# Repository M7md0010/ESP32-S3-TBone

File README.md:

<h1 align="center">ESP32-S3-TBone</h1>

<p align="center">
  <em>Custom T-bone form-factor ESP32-S3 development board engineered to resolve solderless breadboard real estate constraints by exposing dual-sided tie points.</em>
</p>

---

## 📋 Project Overview

The **ESP32-S3-TBone** is a purpose-engineered development board built around the **ESP32-S3-WROOM-1** module. Unlike standard rectangular devkits that monopolize the entire breadboard, the T-bone form factor features a narrowed neck section that straddles the center channel while the head section extends beyond the breadboard edge — freeing up **both sides** of the breadboard for prototyping access to all GPIO tie points.

### Key Design Goals

- **Maximize breadboard usable area** — dual-sided tie point access for all broken-out GPIOs.
- **Signal integrity first** — 4-layer controlled-impedance stackup with dedicated ground and power reference planes.
- **Manufacturing ready** — Gerber-optimized output with DFM rule compliance for standard PCB fabs (JLCPCB, PCBWay, Norisolutions).
- **Mechanical validation** — 3D collision-checked against standard 830-point breadboard models in Fusion 360.

---

## 🏗️ Hardware Architecture & Stackup

### MCU: ESP32-S3-WROOM-1

| Parameter        | Specification                           |
| ---------------- | --------------------------------------- |
| Core             | Xtensa® dual-core 32-bit LX7           |
| Clock            | Up to 240 MHz                           |
| Flash            | 16 MB (Quad SPI)                        |
| SRAM             | 512 KB                                  |
| Connectivity     | Wi-Fi 802.11 b/g/n + Bluetooth 5 (LE)  |
| USB              | Native USB 2.0 OTG + UART via CH343P   |
| GPIO             | Fully broken-out via dual header rows   |

### Onboard Hardware Features & Peripherals

- **I2C Interface:** Dedicated extracted socket/pins for fast and reliable I2C peripheral expansion.
- **Servo Motor Headers:** Onboard header pins specifically broken out for direct servo motor control.
- **Addressable RGB LEDs:** 2× onboard WS2812B RGB LEDs for customizable status indication and visual feedback.
- **Flexible Power Inputs:** Power the board via either of the USB Type-C ports or directly through the header pins.
- **Switchable Breadboard Power Rails:** Two mechanically fit pins designed to drop directly into the breadboard's power rails. Features a dedicated toggle switch to select between **3.3V** and **5V** logic levels for the breadboard.
- **Main Power Switch:** Dedicated ON/OFF toggle switch for main board power.
- **Programmable User Button:** A custom tactile push button hooked up with a pull resistor, ready to be programmed for user input.
- **PTC Thermistors:** Onboard resettable fuses for robust overcurrent protection.

### 4-Layer PCB Stackup

```
┌─────────────────────────────────────────────────────────┐
│  Layer 1 — F.Cu (Top)                                   │
│  → High-density signal routing, component pads,         │
│    USB differential pairs, crystal oscillator traces     │
├─────────────────────────────────────────────────────────┤
│  Layer 2 — In1.Cu (Inner 1)                             │
│  → Solid continuous ground (GND) reference plane        │
│    Provides low-impedance return path for all signals   │
├─────────────────────────────────────────────────────────┤
│  Layer 3 — In2.Cu (Inner 2)                             │
│  → Partitioned low-impedance power planes               │
│    • 3V3 polygon pour — main logic supply               │
│    • 5V rail — USB VBUS passthrough                     │
│    • VBUS — upstream USB input power                    │
├─────────────────────────────────────────────────────────┤
│  Layer 4 — B.Cu (Bottom)                                │
│  → Bottom interconnects, ground return stitching,       │
│    thermal relief pads, and auxiliary signal routing     │
└─────────────────────────────────────────────────────────┘
```

---

## 🔧 Design For Manufacturability (DFM) & Layout

### EMI Shielding — Perimeter Via Stitching
A continuous array of stitching vias along the board perimeter connects the top and bottom ground pours, forming a **Faraday cage** effect. This:
- Contains return currents within the board stackup
- Reduces edge-radiated EMI emissions
- Improves ground plane continuity at board boundaries

### Neck Corner Geometry — CNC Routing Clearance
The interior corners at the T-bone neck-to-head transition use **chamfered/radiused fillets** to accommodate standard CNC routing bit diameters (≥ 0.8 mm). Sharp 90° interior corners are physically impossible to mill and would cause fabrication rejects.

### Soldermask-Clipped Silkscreen
The `--subtract-soldermask` flag was used during Gerber generation to automatically **clip silkscreen artwork** wherever it overlaps exposed copper pads. This prevents:
- Ink-on-pad contamination during soldering
- Poor solder wetting on component pads
- IPC-A-610 Class 2/3 violations

### USB Type-C CC Pull-Down Logic
Both USB-C ports implement the correct **CC1/CC2 pull-down resistor** network (5.1 kΩ to GND) on each Configuration Channel pin, advertising the device as a **UFP (Upstream Facing Port)** sink per USB Type-C spec Rev 2.0. This ensures reliable cable detection and power negotiation with all USB-C hosts and chargers.

---

## 🧊 Mechanical Validation

The board outline (exported as `.step` from KiCad) was imported into **Autodesk Fusion 360** alongside a reference breadboard CAD model to perform:

1. **Collision detection** — verify zero interference between the PCB body and breadboard clips/housing.
2. **Tie-point clearance** — confirm all header pins align with breadboard hole pitch (2.54 mm / 0.1").
3. **Overhang validation** — ensure the head section clears the breadboard edge without cantilever instability.

---

## 📸 Gallery

| Front (3D Render) | Back (3D Render) |
|---|---|
|  |  |

| Front (No Components) | Back (No Components) |
|---|---|
|  |  |

---

## 📁 Directory Structure

```
ESP32-S3-TBone/
├── hardware/
│   ├── schematics/
│   │   ├── schematic.pdf            # Exported schematic drawing (PDF)
│   │   └── v1.0.kicad_sch           # KiCad schematic source
│   ├── pcb/
│   │   ├── v1.0.kicad_pcb           # KiCad PCB layout source
│   │   ├── v1.0.kicad_pro           # KiCad project file
│   │   └── v1.0.kicad_dru           # KiCad design rules
│   ├── gerbers/
│   │   ├── gerbers.zip              # Production-ready Gerber + Drill archive
│   │   ├── v1.0-F_Cu.gtl            # Front copper
│   │   ├── v1.0-In1_Cu.g1           # Inner layer 1 (GND plane)
│   │   ├── v1.0-In2_Cu.g2           # Inner layer 2 (Power planes)
│   │   ├── v1.0-B_Cu.gbl            # Back copper
│   │   ├── v1.0-F_Mask.gts          # Front solder mask
│   │   ├── v1.0-B_Mask.gbs          # Back solder mask
│   │   ├── v1.0-F_Silkscreen.gto    # Front silkscreen
│   │   ├── v1.0-B_Silkscreen.gbo    # Back silkscreen
│   │   ├── v1.0-Edge_Cuts.gm1       # Board outline
│   │   ├── v1.0.drl                 # Excellon drill file
│   │   ├── v1.0-drl_map.gbr         # Drill map (Gerber X2)
│   │   └── ...                      # Additional fabrication layers
│   └── mechanical/
│       ├── ESP32-S3-TBone.step       # 3D STEP assembly export
│       ├── Breadboard.fbx            # Breadboard reference model
│       └── breadboard-reference.glb  # Breadboard GLB model
├── docs/
│   └── images/
│       ├── 3d-front.png              # Front 3D render
│       ├── 3d-back.png               # Back 3D render
│       ├── 3d-front-no-components.png
│       ├── 3d-back-no-components.png
│       ├── breadboard-fit.png        # Breadboard fit verification
│       └── comparison.png            # Size comparison
├── .gitignore
├── LICENSE                            # MIT License
└── README.md                          # This file
```

---

## 🛠️ Regenerating Manufacturing Files

If you modify the KiCad source files, regenerate all outputs using `kicad-cli`:

```bash
# Gerber layers (with soldermask-clipped silkscreen)
kicad-cli pcb export gerbers --subtract-soldermask \
  -o hardware/gerbers/ hardware/pcb/v1.0.kicad_pcb

# Excellon drill files + Gerber X2 drill map
kicad-cli pcb export drill --generate-map --map-format gerberx2 \
  -o hardware/gerbers/ hardware/pcb/v1.0.kicad_pcb

# Schematic PDF
kicad-cli sch export pdf \
  -o hardware/schematics/schematic.pdf hardware/schematics/v1.0.kicad_sch

# STEP 3D assembly (skip DNP, substitute models)
kicad-cli pcb export step --no-dnp --subst-models \
  -o hardware/mechanical/ESP32-S3-TBone.step hardware/pcb/v1.0.kicad_pcb
```

---

## 📜 License

This project is licensed under the **MIT License** — see the [LICENSE](./LICENSE) file for details.

---

<p align="center">
  <sub>Designed & engineered by <a href="https://github.com/M7md0010">@M7md0010</a></sub>
</p>

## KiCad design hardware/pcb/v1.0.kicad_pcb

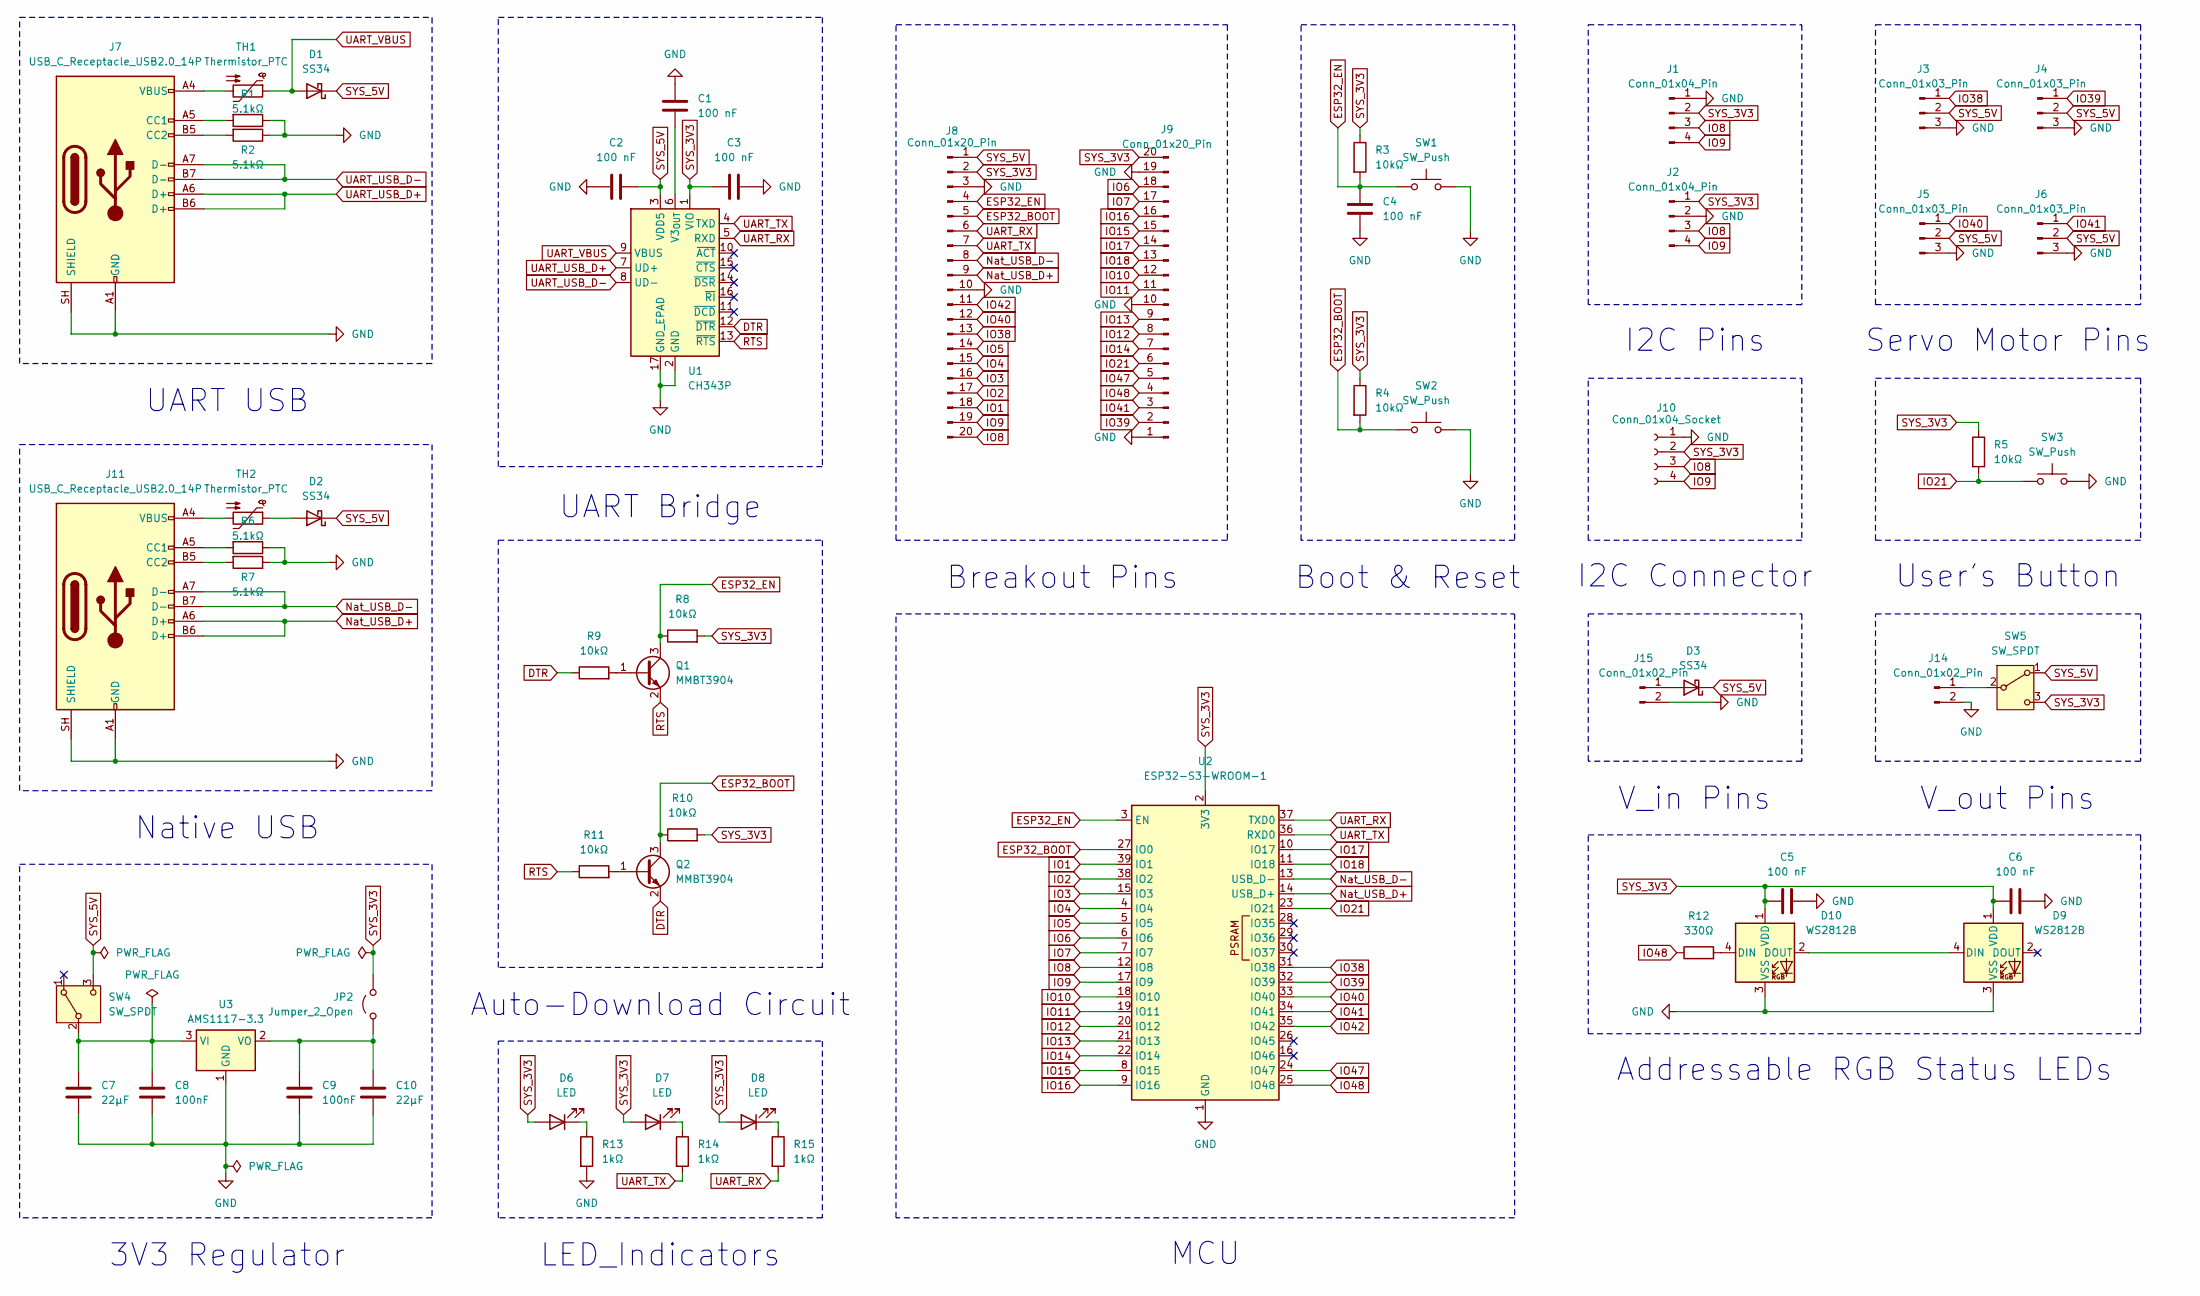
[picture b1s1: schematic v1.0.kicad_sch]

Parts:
C1, C2, C3, C4, C5, C6: 100 nF; C_0201_0603Metric
C7, C10: 22μF; C_1206_3216Metric
C8, C9: 100nF; C_0201_0603Metric
D1, D2, D3: SS34; D_SMA
D6, D7, D8: LED; LED_0805_2012Metric
D9, D10: WS2812B; LED_WS2812B_PLCC4_5.0x5.0mm_P3.2mm
J1, J2: Conn_01x04_Pin; PinSocket_1x04_P2.54mm_Vertical
J3, J4, J5, J6: Conn_01x03_Pin; PinHeader_1x03_P2.54mm_Vertical
J7, J11: USB_C_Receptacle_USB2.0_14P; USB_C_Receptacle_HRO_TYPE-C-31-M-12
J8, J9: Conn_01x20_Pin; PinHeader_1x20_P2.54mm_Vertical
J10: Conn_01x04_Socket; JST_EH_S4B-EH_1x04_P2.50mm_Horizontal
J14, J15: Conn_01x02_Pin; PinHeader_1x02_P2.54mm_Vertical
JP2: Jumper_2_Open; SolderJumper-2_P1.3mm_Open_RoundedPad1.0x1.5mm
Q1, Q2: MMBT3904; SOT-23
R1, R2, R6, R7: 5.1kΩ; R_0603_1608Metric
R3, R4, R5, R8, R9, R10, R11: 10kΩ; R_0603_1608Metric
R12: 330Ω; R_0603_1608Metric
R13, R14, R15: 1kΩ; R_0603_1608Metric
SW1, SW2, SW3: SW_Push; SW_SPST_PTS645Sx43SMTR92
SW4: SW_SPDT; SW_SPDT_PCM12
SW5: SW_SPDT; SW_Slide_SPDT_Straight_CK_OS102011MS2Q
TH1, TH2: Thermistor_PTC; Fuse_1206_3216Metric
U1: CH343P; WCH_QFN-16-1EP_3x3mm_P0.5mm_EP1.8x1.8mm
U2: ESP32-S3-WROOM-1
U3: AMS1117-3.3; SOT-223-3_TabPin2

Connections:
DTR: Q2.2 (E), R9.1, U1.12 (~DTR)
ESP32_BOOT: J8.5, Q2.3 (C), R4.2, R10.1, SW2.1, U2.27 (IO0)
ESP32_EN: C4.1, J8.4, Q1.3 (C), R3.2, R8.1, SW1.1, U2.3 (EN)
GND: C1.1, C2.2, C3.1, C4.2, C5.1, C6.1, C7.2, C8.2, C9.2, C10.2, D9.3 (VSS), D10.3 (VSS), J1.1, J2.2, J3.3, J4.3, J5.3, J6.3, J7.A1 (GND), J7.A12 (GND), J7.B1 (GND), J7.B12 (GND), J7.SH (SHIELD), J8.3, J8.10, J9.1, J9.10, J9.19, J10.1, J11.A1 (GND), J11.A12 (GND), J11.B1 (GND), J11.B12 (GND), J11.SH (SHIELD), J14.2, J15.2, R1.1, R2.1, R6.1, R7.1, R13.2, SW1.2, SW2.2, SW3.2, U1.2 (GND), U1.17 (GND_EPAD), U2.1 (GND), U2.40 (GND), U2.41 (GND), U3.1 (GND)
IO1: J8.18, U2.39 (IO1)
IO2: J8.17, U2.38 (IO2)
IO3: J8.16, U2.15 (IO3)
IO4: J8.15, U2.4 (IO4)
IO5: J8.14, U2.5 (IO5)
IO6: J9.18, U2.6 (IO6)
IO7: J9.17, U2.7 (IO7)
IO8: J1.3, J2.3, J8.20, J10.3, U2.12 (IO8)
IO9: J1.4, J2.4, J8.19, J10.4, U2.17 (IO9)
IO10: J9.12, U2.18 (IO10)
IO11: J9.11, U2.19 (IO11)
IO12: J9.8, U2.20 (IO12)
IO13: J9.9, U2.21 (IO13)
IO14: J9.7, U2.22 (IO14)
IO15: J9.15, U2.8 (IO15)
IO16: J9.16, U2.9 (IO16)
IO17: J9.14, U2.10 (IO17)
IO18: J9.13, U2.11 (IO18)
IO21: J9.6, R5.2, SW3.1, U2.23 (IO21)
IO38: J3.1, J8.13, U2.31 (IO38)
IO39: J4.1, J9.2, U2.32 (IO39)
IO40: J5.1, J8.12, U2.33 (IO40)
IO41: J6.1, J9.3, U2.34 (IO41)
IO42: J8.11, U2.35 (IO42)
IO47: J9.5, U2.24 (IO47)
IO48: J9.4, R12.1, U2.25 (IO48)
Nat_USB_D+: J8.9, J11.A6 (D+), J11.B6 (D+), U2.14 (USB_D+)
Nat_USB_D-: J8.8, J11.A7 (D-), J11.B7 (D-), U2.13 (USB_D-)
unnamed: D2.2 (A), TH2.1
unnamed: D3.2 (A), J15.1
unnamed: D6.1 (K), R13.1
unnamed: D7.1 (K), R14.1
unnamed: D8.1 (K), R15.1
unnamed: D10.4 (DIN), R12.2
unnamed: D9.4 (DIN), D10.2 (DOUT)
unnamed: J7.A5 (CC1), R1.2
unnamed: J7.B5 (CC2), R2.2
unnamed: J7.A4 (VBUS), J7.A9 (VBUS), J7.B4 (VBUS), J7.B9 (VBUS), TH1.2
unnamed: J11.A5 (CC1), R6.2
unnamed: J11.B5 (CC2), R7.2
unnamed: J11.A4 (VBUS), J11.A9 (VBUS), J11.B4 (VBUS), J11.B9 (VBUS), TH2.2
unnamed: J14.1, SW5.2 (B)
unnamed: C9.1, C10.1, JP2.1 (A), U3.2 (VO)
unnamed: Q1.1 (B), R9.2
unnamed: Q2.1 (B), R11.2
unnamed: C7.1, C8.1, SW4.2 (B), U3.3 (VI)
unnamed: C1.2, U1.6 (V3_{OUT})
RTS: Q1.2 (E), R11.1, U1.13 (~RTS)
SYS_3V3: C3.2, C5.2, C6.2, D6.2 (A), D7.2 (A), D8.2 (A), D9.1 (VDD), D10.1 (VDD), J1.2, J2.1, J8.2, J9.20, J10.2, JP2.2 (B), R3.1, R4.1, R5.1, R8.2, R10.2, SW5.3 (C), U1.1 (VIO), U2.2 (3V3)
SYS_5V: C2.1, D1.1 (K), D2.1 (K), D3.1 (K), J3.2, J4.2, J5.2, J6.2, J8.1, SW4.3 (C), SW5.1 (A), U1.3 (VDD5)
UART_RX: J8.6, R15.2, U1.5 (RXD), U2.37 (TXD0)
UART_TX: J8.7, R14.2, U1.4 (TXD), U2.36 (RXD0)
UART_USB_D+: J7.A6 (D+), J7.B6 (D+), U1.7 (UD+)
UART_USB_D-: J7.A7 (D-), J7.B7 (D-), U1.8 (UD-)
UART_VBUS: D1.2 (A), TH1.1, U1.9 (VBUS)

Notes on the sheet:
Servo Motor Pins
Auto-Download Circuit
UART USB
MCU
LED_Indicators
3V3 Regulator
Boot & Reset
Breakout Pins
UART Bridge
Native USB
User's Button
I2C Connector
V_in Pins
I2C Pins
Addressable RGB Status LEDs
V_out Pins

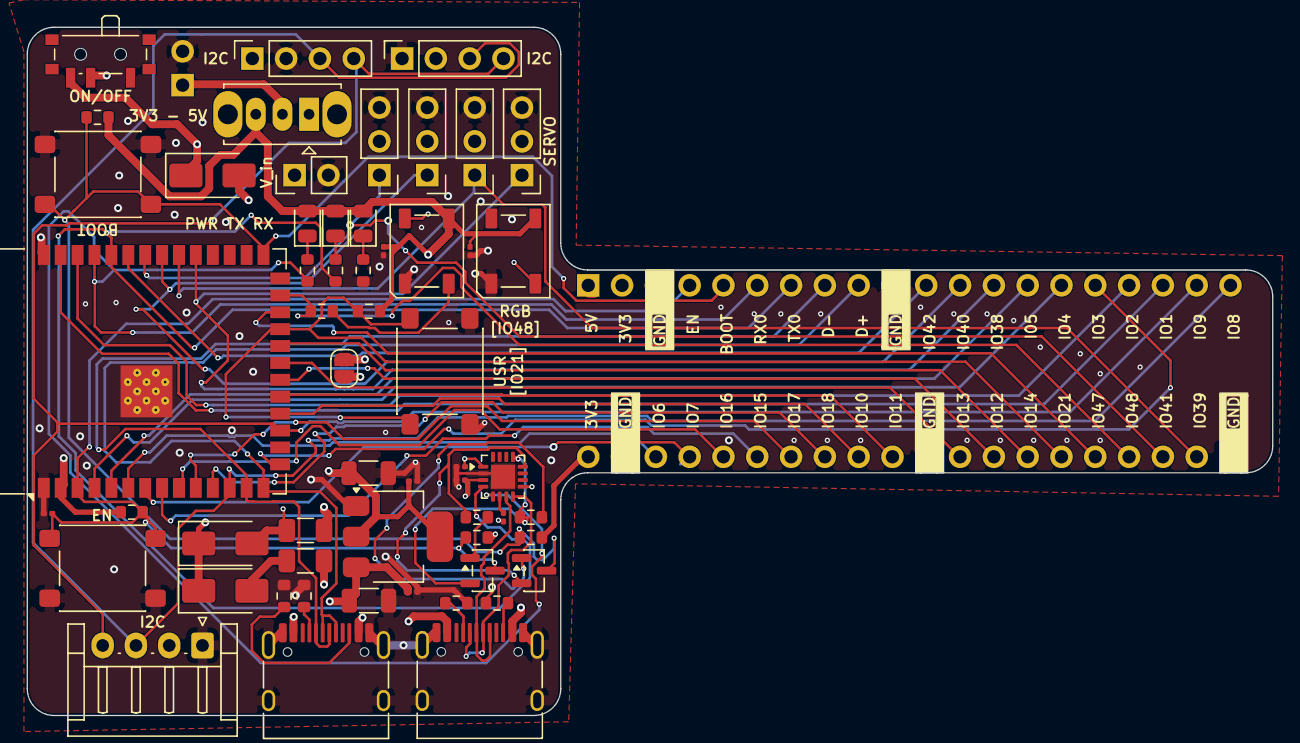
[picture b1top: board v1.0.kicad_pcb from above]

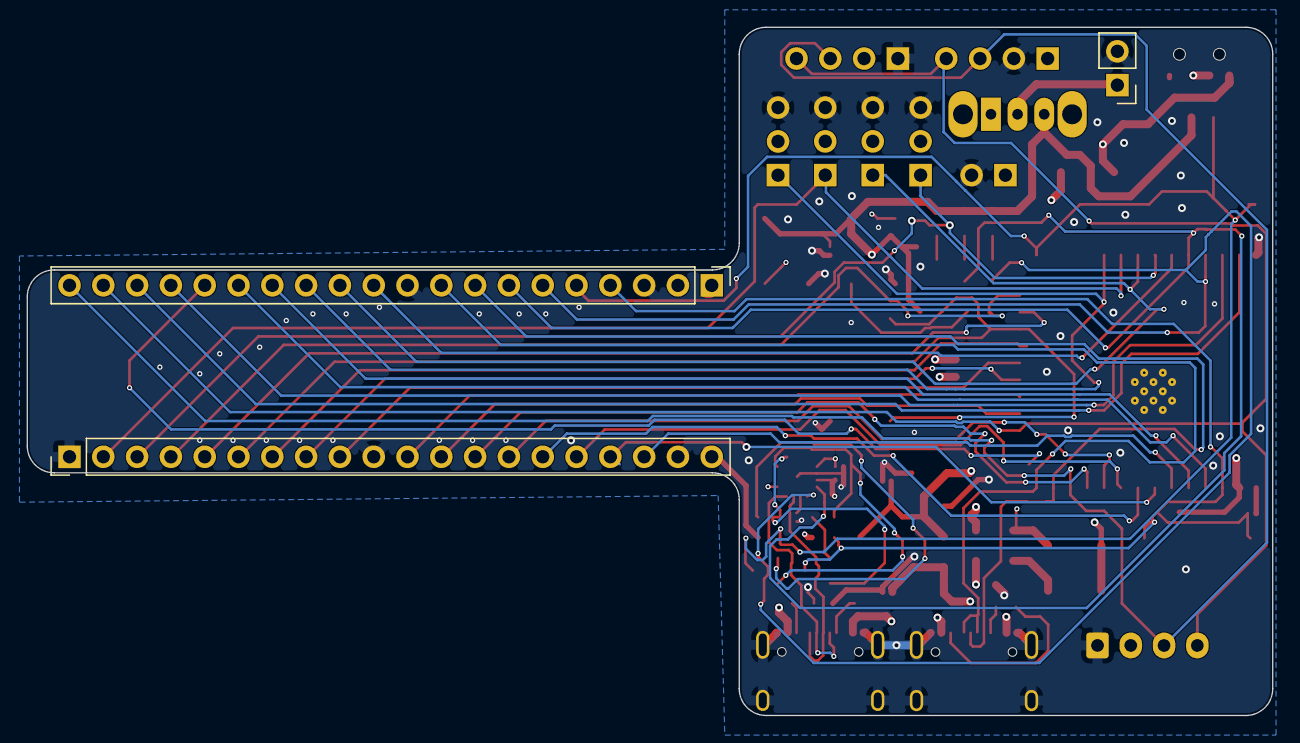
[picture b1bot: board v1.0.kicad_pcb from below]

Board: 4 copper layers, 93.6 x 51.7 mm, 59 parts (3 on the bottom side), 59 nets.

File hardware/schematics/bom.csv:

"Refs","Value","Footprint","Qty","DNP"
"C1","100 nF","Capacitor_SMD:C_0201_0603Metric","1",""
"C2","100 nF","Capacitor_SMD:C_0201_0603Metric","1",""
"C3","100 nF","Capacitor_SMD:C_0201_0603Metric","1",""
"C4","100 nF","Capacitor_SMD:C_0201_0603Metric","1",""
"C5","100 nF","Capacitor_SMD:C_0201_0603Metric","1",""
"C6","100 nF","Capacitor_SMD:C_0201_0603Metric","1",""
"C7","22μF","Capacitor_SMD:C_1206_3216Metric","1",""
"C8","100nF","Capacitor_SMD:C_0201_0603Metric","1",""
"C9","100nF","Capacitor_SMD:C_0201_0603Metric","1",""
"C10","22μF","Capacitor_SMD:C_1206_3216Metric","1",""
"D1","SS34","Diode_SMD:D_SMA","1",""
"D2","SS34","Diode_SMD:D_SMA","1",""
"D3","SS34","Diode_SMD:D_SMA","1",""
"D6","LED","LED_SMD:LED_0805_2012Metric","1",""
"D7","LED","LED_SMD:LED_0805_2012Metric","1",""
"D8","LED","LED_SMD:LED_0805_2012Metric","1",""
"D9","WS2812B","LED_SMD:LED_WS2812B_PLCC4_5.0x5.0mm_P3.2mm","1",""
"D10","WS2812B","LED_SMD:LED_WS2812B_PLCC4_5.0x5.0mm_P3.2mm","1",""
"J1","Conn_01x04_Pin","Connector_PinSocket_2.54mm:PinSocket_1x04_P2.54mm_Vertical","1",""
"J2","Conn_01x04_Pin","Connector_PinSocket_2.54mm:PinSocket_1x04_P2.54mm_Vertical","1",""
"J3","Conn_01x03_Pin","Connector_PinHeader_2.54mm:PinHeader_1x03_P2.54mm_Vertical","1",""
"J4","Conn_01x03_Pin","Connector_PinHeader_2.54mm:PinHeader_1x03_P2.54mm_Vertical","1",""
"J5","Conn_01x03_Pin","Connector_PinHeader_2.54mm:PinHeader_1x03_P2.54mm_Vertical","1",""
"J6","Conn_01x03_Pin","Connector_PinHeader_2.54mm:PinHeader_1x03_P2.54mm_Vertical","1",""
"J7","USB_C_Receptacle_USB2.0_14P","Connector_USB:USB_C_Receptacle_HRO_TYPE-C-31-M-12","1",""
"J8","Conn_01x20_Pin","Connector_PinHeader_2.54mm:PinHeader_1x20_P2.54mm_Vertical","1",""
"J9","Conn_01x20_Pin","Connector_PinHeader_2.54mm:PinHeader_1x20_P2.54mm_Vertical","1",""
"J10","Conn_01x04_Socket","Connector_JST:JST_EH_S4B-EH_1x04_P2.50mm_Horizontal","1",""
"J11","USB_C_Receptacle_USB2.0_14P","Connector_USB:USB_C_Receptacle_HRO_TYPE-C-31-M-12","1",""
"J14","Conn_01x02_Pin","Connector_PinHeader_2.54mm:PinHeader_1x02_P2.54mm_Vertical","1",""
"J15","Conn_01x02_Pin","Connector_PinHeader_2.54mm:PinHeader_1x02_P2.54mm_Vertical","1",""
"JP2","Jumper_2_Open","Jumper:SolderJumper-2_P1.3mm_Open_RoundedPad1.0x1.5mm","1",""
"Q1","MMBT3904","Package_TO_SOT_SMD:SOT-23","1",""
"Q2","MMBT3904","Package_TO_SOT_SMD:SOT-23","1",""
"R1","5.1kΩ","Resistor_SMD:R_0603_1608Metric","1",""
"R2","5.1kΩ","Resistor_SMD:R_0603_1608Metric","1",""
"R3","10kΩ","Resistor_SMD:R_0603_1608Metric","1",""
"R4","10kΩ","Resistor_SMD:R_0603_1608Metric","1",""
"R5","10kΩ","Resistor_SMD:R_0603_1608Metric","1",""
"R6","5.1kΩ","Resistor_SMD:R_0603_1608Metric","1",""
"R7","5.1kΩ","Resistor_SMD:R_0603_1608Metric","1",""
"R8","10kΩ","Resistor_SMD:R_0603_1608Metric","1",""
"R9","10kΩ","Resistor_SMD:R_0603_1608Metric","1",""
"R10","10kΩ","Resistor_SMD:R_0603_1608Metric","1",""
"R11","10kΩ","Resistor_SMD:R_0603_1608Metric","1",""
"R12","330Ω","Resistor_SMD:R_0603_1608Metric","1",""
"R13","1kΩ","Resistor_SMD:R_0603_1608Metric","1",""
"R14","1kΩ","Resistor_SMD:R_0603_1608Metric","1",""
"R15","1kΩ","Resistor_SMD:R_0603_1608Metric","1",""
"SW1","SW_Push","Button_Switch_SMD:SW_SPST_PTS645Sx43SMTR92","1",""
"SW2","SW_Push","Button_Switch_SMD:SW_SPST_PTS645Sx43SMTR92","1",""
"SW3","SW_Push","Button_Switch_SMD:SW_SPST_PTS645Sx43SMTR92","1",""
"SW4","SW_SPDT","Button_Switch_SMD:SW_SPDT_PCM12","1",""
"SW5","SW_SPDT","Button_Switch_THT:SW_Slide_SPDT_Straight_CK_OS102011MS2Q","1",""
"TH1","Thermistor_PTC","Fuse:Fuse_1206_3216Metric","1",""
"TH2","Thermistor_PTC","Fuse:Fuse_1206_3216Metric","1",""
"U1","CH343P","Package_DFN_QFN:WCH_QFN-16-1EP_3x3mm_P0.5mm_EP1.8x1.8mm","1",""
"U2","ESP32-S3-WROOM-1","RF_Module:ESP32-S3-WROOM-1","1",""
"U3","AMS1117-3.3","Package_TO_SOT_SMD:SOT-223-3_TabPin2","1",""

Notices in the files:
README.md:
License: Non-Commercial
